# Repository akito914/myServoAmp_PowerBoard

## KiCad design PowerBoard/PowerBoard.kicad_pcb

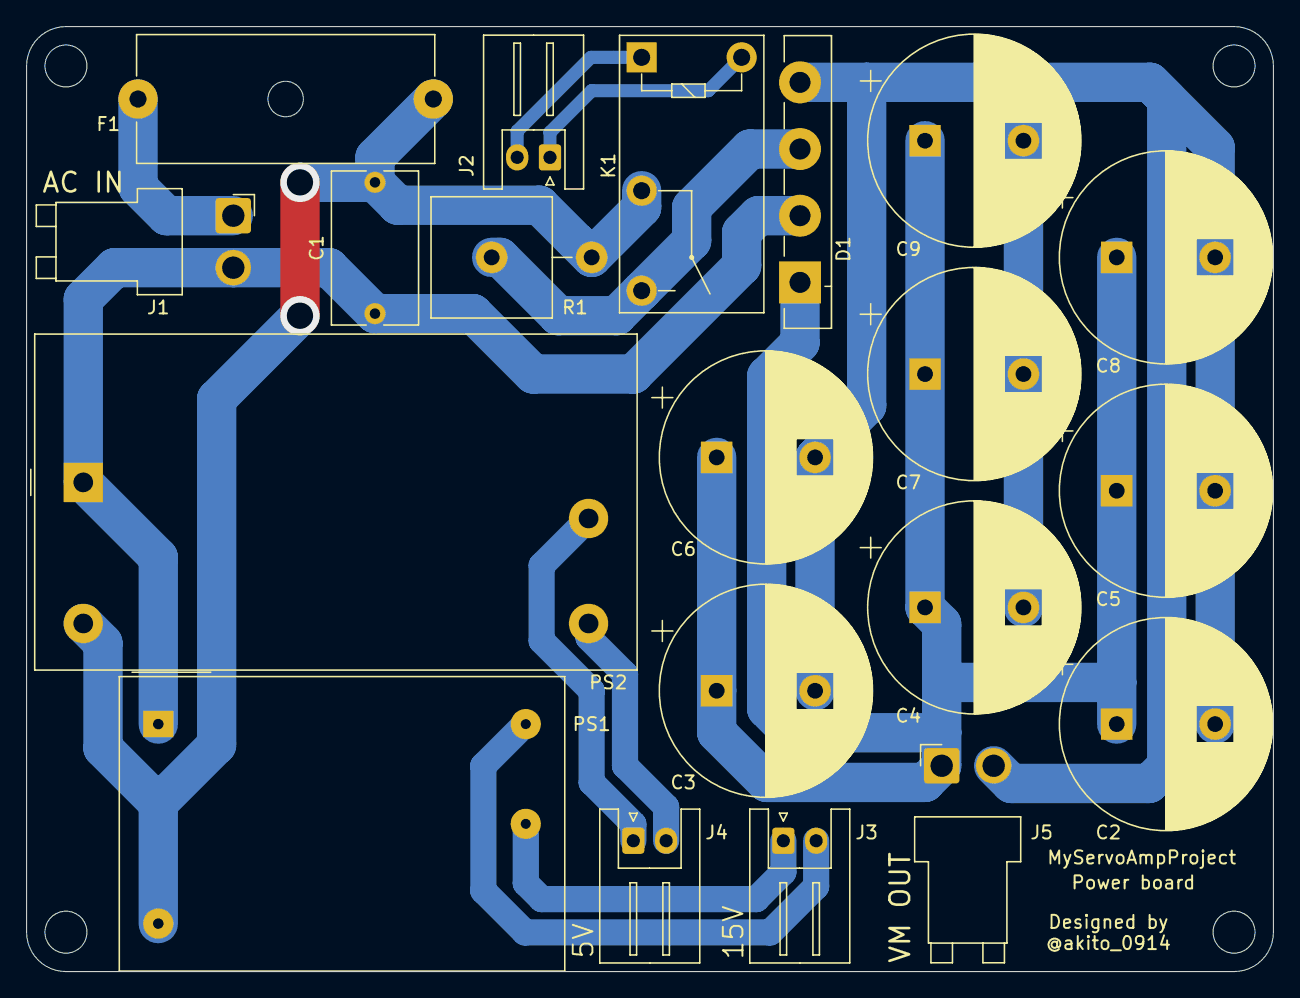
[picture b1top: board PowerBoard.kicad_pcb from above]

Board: 2 copper layers, 95.0 x 72.0 mm, 24 parts (0 on the bottom side), 12 nets.

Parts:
C1: 0.1u; C_Rect_L11.5mm_W6.4mm_P10.00mm_MKT
C2, C3, C4, C5, C6, C7, C8, C9: 150u; CP_Radial_D16.0mm_P7.50mm
D1: GBU1010TB; Diode_Bridge_Vishay_GBU
F1: 10A; Fuseholder_Cylinder-5x20mm_Schurter_0031_8201_Horizontal_Op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
H1, H2, H3, H4: MountingHole; MountingHole_3.2mm_M3
J1: AC_IN; JST_VH_B2PS-VH_1x02_P3.96mm_Horizontal
J2: RelayCoil; JST_XH_S2B-XH-A_1x02_P2.50mm_Horizontal
J3: GATE_DRIVE; JST_XH_S2B-XH-A_1x02_P2.50mm_Horizontal
J4: LOGIC; JST_XH_S2B-XH-A_1x02_P2.50mm_Horizontal
J5: DC_LINK; JST_VH_B2PS-VH_1x02_P3.96mm_Horizontal
K1: ALQ305; Relay_SPST_Omron-G5Q-1A
PS1: IRM-02-15; Converter_ACDC_MeanWell_IRM-02-xx_THT
PS2: IRM-05-5; Converter_ACDC_MeanWell_IRM-05-xx_THT
R1: 3R; R_Axial_Power_L25.0mm_W9.0mm_P7.62mm_Vertical

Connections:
unnamed: C1.1, F1.1, K1.2, PS1.2, PS2.2, R1.2
unnamed: C1.2, D1.2, J1.2, PS1.1, PS2.1
unnamed: C2.1, C3.1, C4.1, C5.1, C6.1, C7.1, C8.1, C9.1, D1.1, J5.1
unnamed: C2.2, C3.2, C4.2, C5.2, C6.2, C7.2, C8.2, C9.2, D1.4, J5.2
unnamed: D1.3, K1.3, R1.1
unnamed: F1.2, J1.1
unnamed: J2.1, K1.5
unnamed: J2.2, K1.1
unnamed: J3.1, PS1.4
unnamed: J3.2, PS1.3
unnamed: J4.1, PS2.4
unnamed: J4.2, PS2.3

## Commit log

2020-04-15 回路図完成
2020-04-15 部品載せてみた，無理そう
2020-04-16 コンデンサを一つ減らして配線完了
2020-04-16 固定穴のレジスト除去
2020-05-02 コネクタ配置変更，シルク調整
2020-05-02 シルク調整
2020-05-02 ガーバー書き出し
